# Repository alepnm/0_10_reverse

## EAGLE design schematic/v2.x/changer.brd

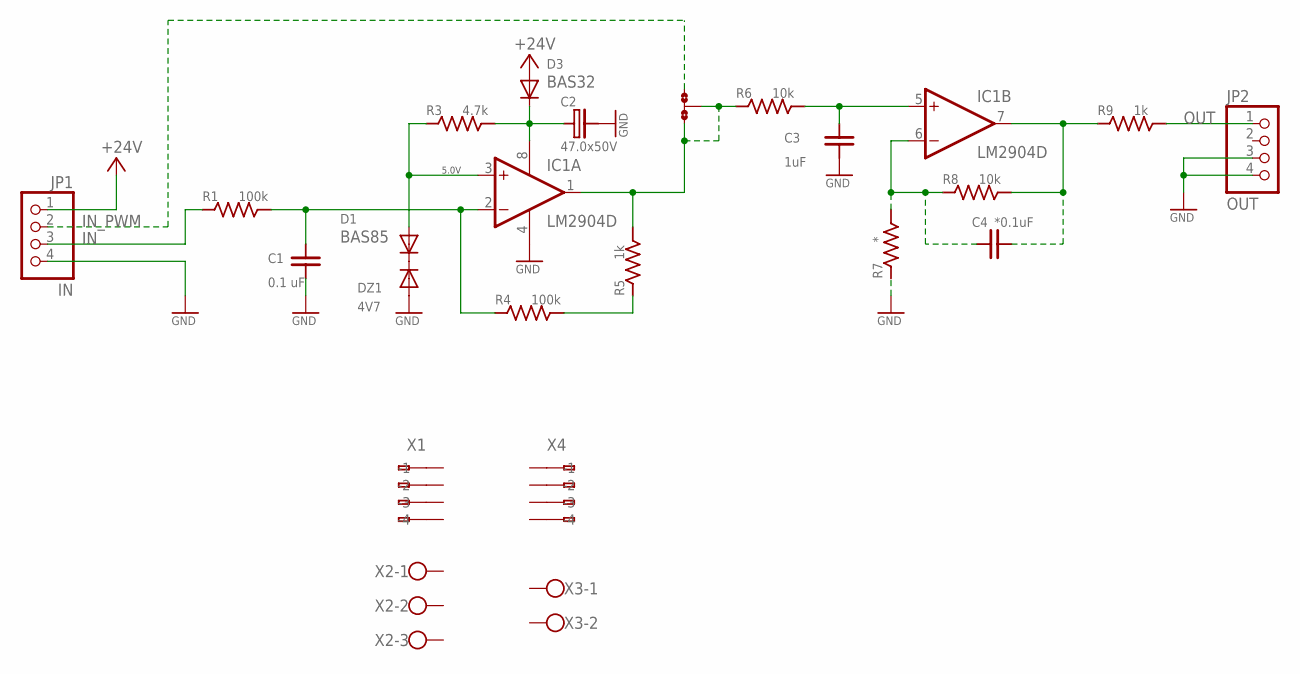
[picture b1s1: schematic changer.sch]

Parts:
C1: 0.1 uF; C0805
C2: 47.0x50V; E2,5-5
C3: 1uF; C0805
C4: *0.1uF; C0805
D1: BAS85; MINIMELF
D3: BAS32; MINIMELF
DZ1: 4V7; MINIMELF
IC1: LM2904D; SO08
JMP1: JUMP; A0R-JMP
JP1: IN; 1X04
JP2: OUT; 1X04
R1, R4: 100k; R0805
R3: 4.7k; R0805
R5, R9: 1k; R0805
R6, R8: 10k; R0805
R7: *; R0805
X1, X4: 233-104
X2: W237-103
X3: W237-102

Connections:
+24V: D3.A, JP1.1
GND: C1.1, C2.-, C3.1, DZ1.A, IC1.4 (V-), JP1.4, JP2.3, JP2.4, R7.1
IN: JP1.3, R1.1
IN_PWM: JMP1.1, JP1.2
unnamed: D1.C, DZ1.C
unnamed: D1.A, IC1.3 (+IN), R3.1
unnamed: C1.2, IC1.2 (-IN), R1.2, R4.1
unnamed: C3.2, IC1.5 (+IN), R6.2
unnamed: R4.2, R5.1
unnamed: C4.2, IC1.7 (OUT), R8.2, R9.1
unnamed: C4.1, IC1.6 (-IN), R7.2, R8.1
unnamed: C2.+, D3.C, IC1.8 (V+), R3.2
unnamed: IC1.1 (OUT), JMP1.2, JMP1.3, R5.2, R6.1
OUT: JP2.1, R9.2

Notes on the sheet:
5.0V

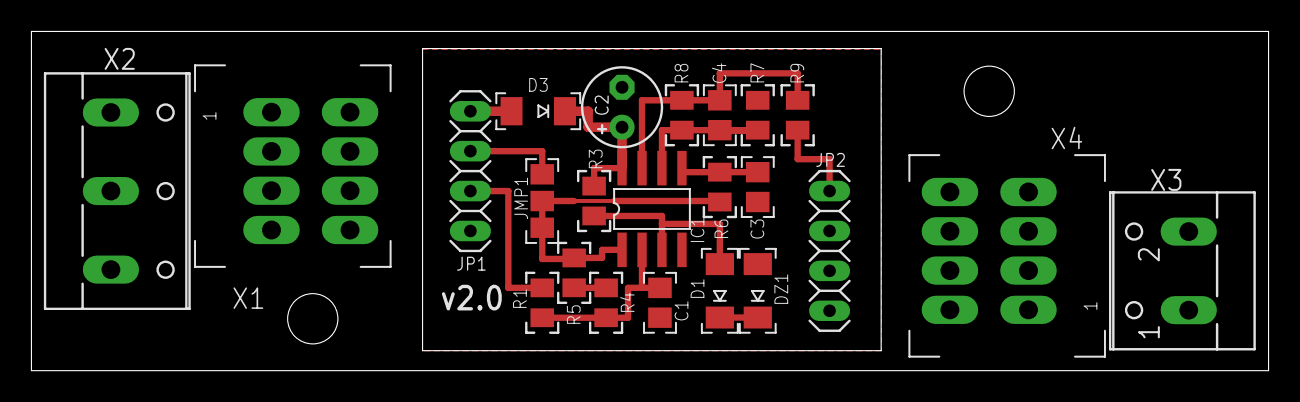
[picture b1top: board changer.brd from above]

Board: 2 copper layers, 78.7 x 21.6 mm, 23 parts (0 on the bottom side), 14 nets.

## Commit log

2018-07-31 pradinis inicializavimas
2018-07-31 dokumentacijos ruosimas - sugeneruotas 3d modelis
2019-03-21 sugeneruoti postscript failai fotosablonui
